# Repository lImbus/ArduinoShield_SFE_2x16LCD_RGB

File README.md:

ArduinoShield_SFE_2x16LCD_RGB
=============================

An Arduino Shield for the Sparkfun "Basic 16x2 Character LCD - RGB Backlight 5V" LCD-10862

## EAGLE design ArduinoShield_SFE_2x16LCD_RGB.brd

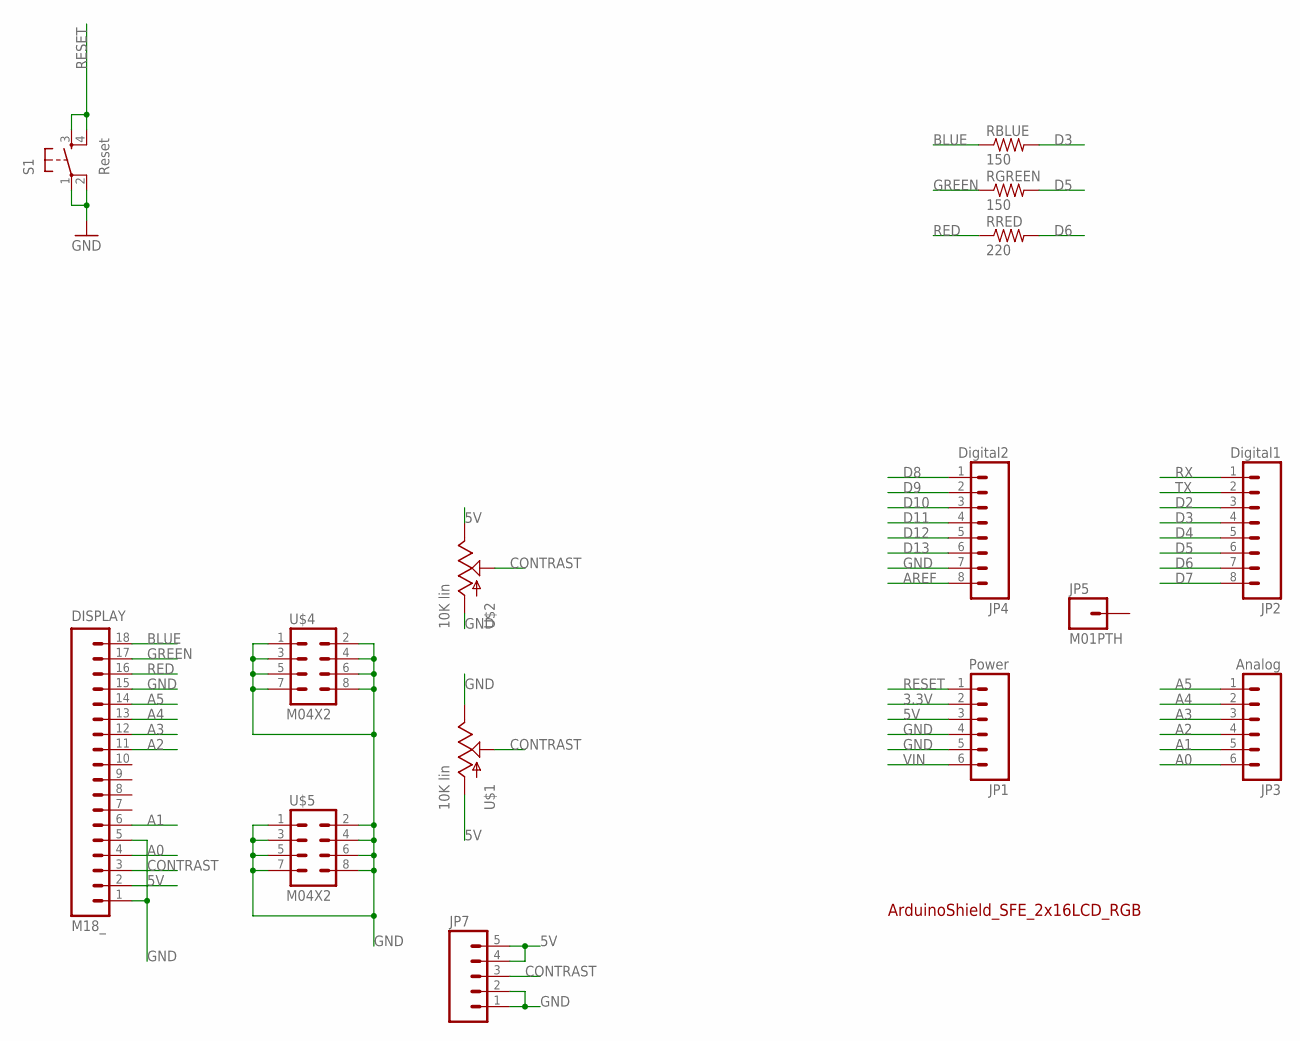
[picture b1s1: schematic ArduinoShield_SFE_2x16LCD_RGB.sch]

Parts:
DISPLAY: M18_; 1X18
JP1: Power; 1X06
JP2: Digital1; 1X08
JP3: Analog; 1X06
JP4: Digital2; 1X08
JP5: M01PTH; 1X01
JP7: M05PTH_LONGPADS; 1X05_LONGPADS
RBLUE: 150; AXIAL-0.5
RGREEN: 150; AXIAL-0.5
RRED: 220; AXIAL-0.5
S1: Reset; TACTILE-PTH
U$1: 10K lin; ALPS_POT
U$2: 10K lin; POT_ALPHA_RV16AF-20
U$4, U$5: M04X2; 2X4

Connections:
3.3V: JP1.2
5V: DISPLAY.2, JP1.3, JP7.4, JP7.5, U$1.P$3 (A), U$2.3 (E)
A0: DISPLAY.4, JP3.6
A1: DISPLAY.6, JP3.5
A2: DISPLAY.11, JP3.4
A3: DISPLAY.12, JP3.3
A4: DISPLAY.13, JP3.2
A5: DISPLAY.14, JP3.1
AREF: JP4.8
BLUE: DISPLAY.18, RBLUE.P$1 (1)
CONTRAST: DISPLAY.3, JP7.3, U$1.P$2 (S), U$2.2 (S)
D2: JP2.3
D3: JP2.4, RBLUE.P$2 (2)
D4: JP2.5
D5: JP2.6, RGREEN.P$2 (2)
D6: JP2.7, RRED.P$2 (2)
D7: JP2.8
D8: JP4.1
D9: JP4.2
D10: JP4.3
D11: JP4.4
D12: JP4.5
D13: JP4.6
GND: DISPLAY.1, DISPLAY.5, DISPLAY.15, JP1.4, JP1.5, JP4.7, JP7.1, JP7.2, S1.1, S1.2, U$1.P$1 (E), U$2.1 (A), U$4.1, U$4.2, U$4.3, U$4.4, U$4.5, U$4.6, U$4.7, U$4.8, U$5.1, U$5.2, U$5.3, U$5.4, U$5.5, U$5.6, U$5.7, U$5.8
GREEN: DISPLAY.17, RGREEN.P$1 (1)
RED: DISPLAY.16, RRED.P$1 (1)
RESET: JP1.1, S1.3, S1.4
RX: JP2.1
TX: JP2.2
VIN: JP1.6

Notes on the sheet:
ArduinoShield_SFE_2x16LCD_RGB

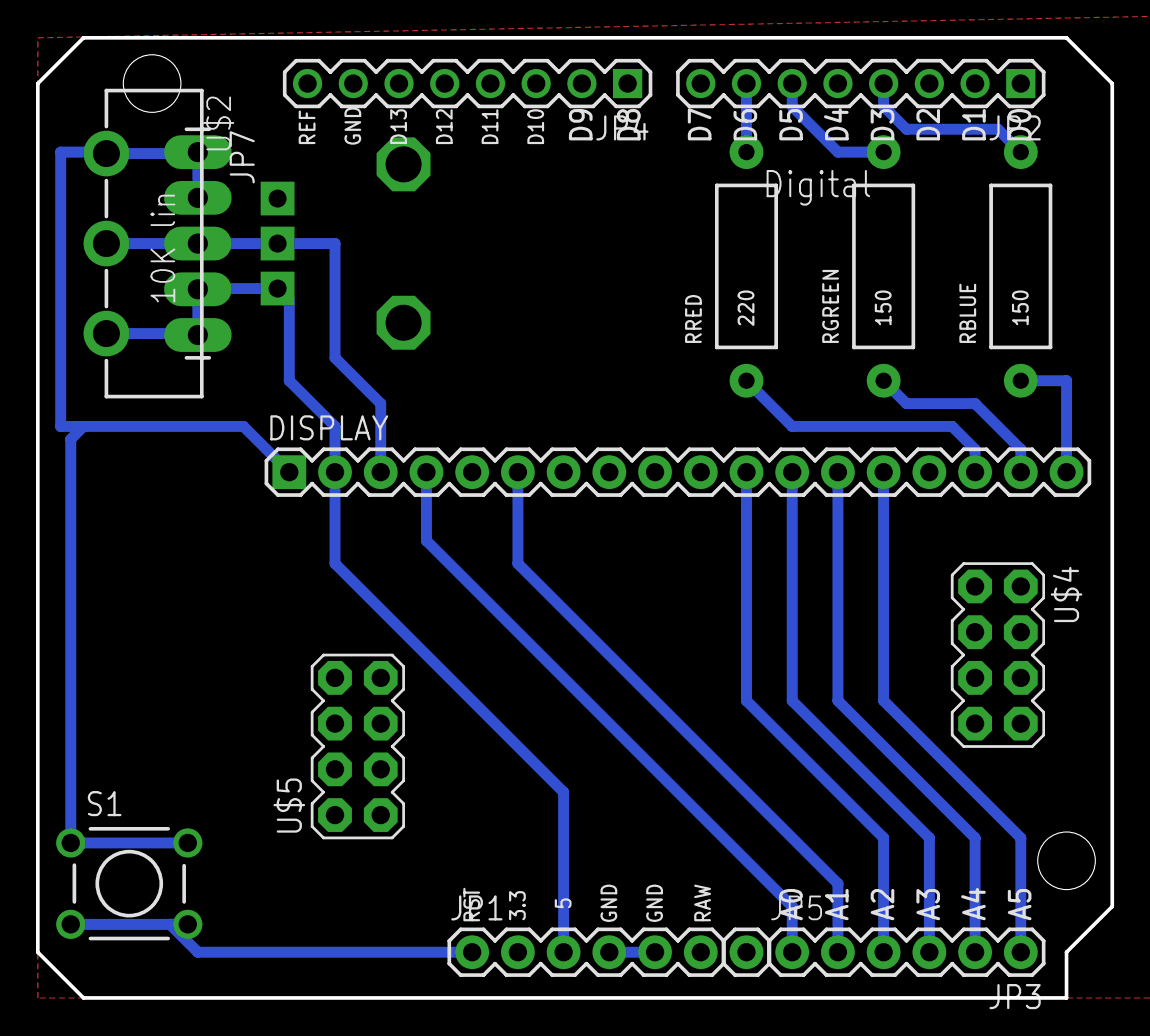
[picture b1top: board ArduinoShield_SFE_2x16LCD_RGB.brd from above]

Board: 2 copper layers, 59.7 x 53.3 mm, 15 parts (0 on the bottom side), 16 nets.

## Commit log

2012-09-21 this is the first version in repo, with all corrections and the better pin layout
